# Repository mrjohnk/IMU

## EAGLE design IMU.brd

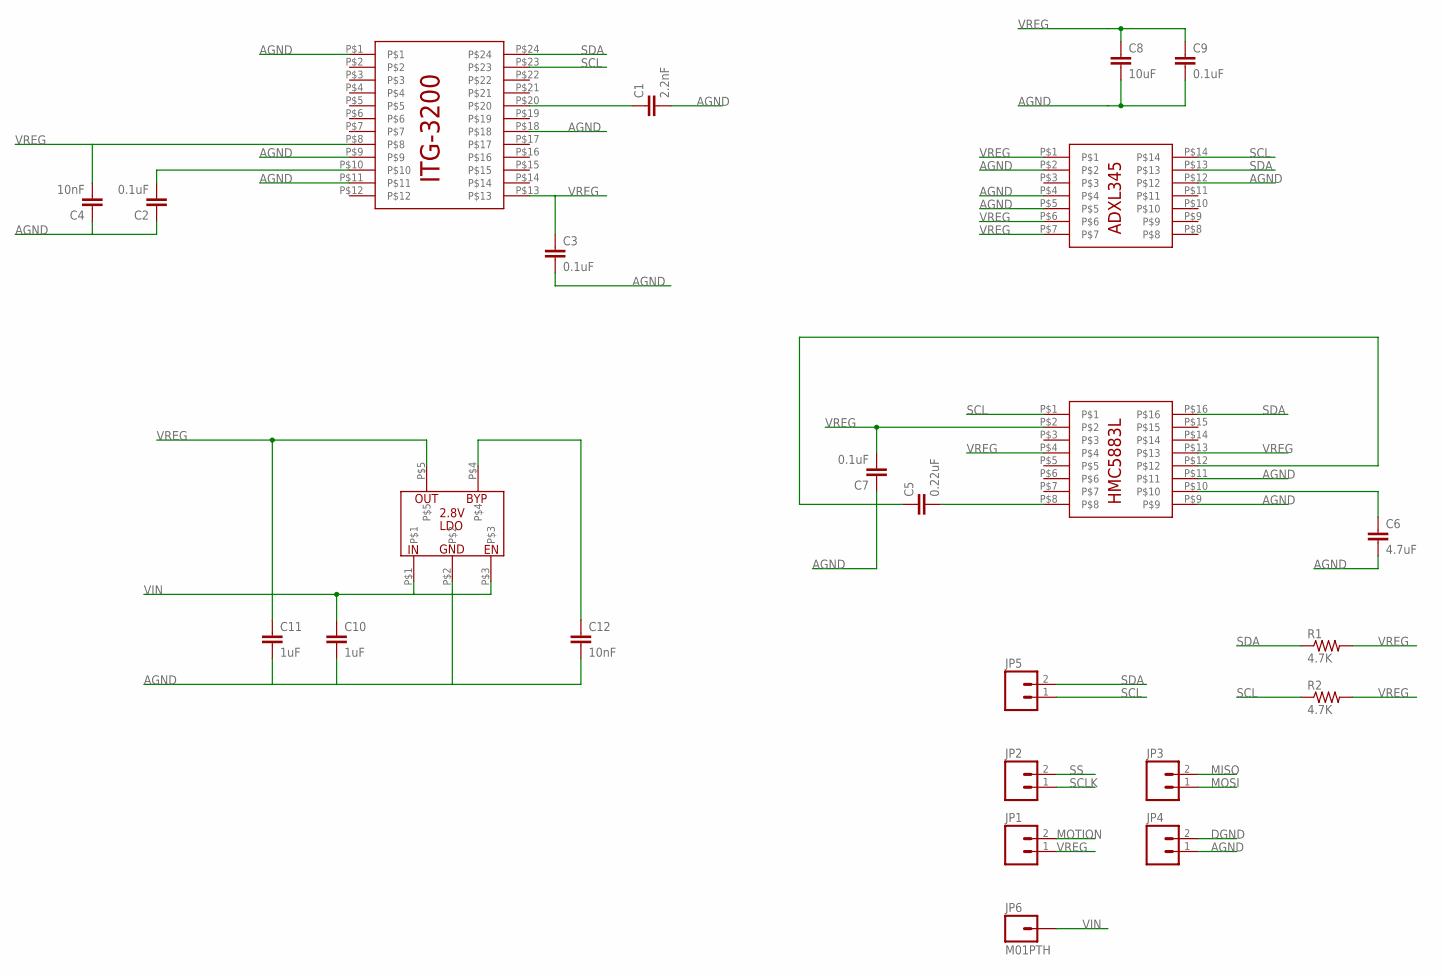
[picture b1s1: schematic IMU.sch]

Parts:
C1: 2.2nF; 0603-CAP
C2, C3, C7, C9: 0.1uF; 0603-CAP
C4, C12: 10nF; 0603-CAP
C5: 0.22uF; 0603-CAP
C6: 4.7uF; 0603-CAP
C8: 10uF; 0603-CAP
C10, C11: 1uF; 0603-CAP
JP1, JP2, JP3, JP4, JP5: M02PTH; 1X02
JP6: M01PTH; 1X01
R1, R2: 4.7K; 0603-RES
U$2: ADXL345
U$3: HMC5883L
U$4: ITG-3200
U$5: NCP700BMT28TBG__2.8V_LDO

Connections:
AGND: C1.2, C2.1, C3.2, C4.1, C6.2, C7.1, C8.2, C9.2, C10.2, C11.2, C12.2, JP4.1, U$2.P$2, U$2.P$4, U$2.P$5, U$2.P$12, U$3.P$9, U$3.P$11, U$4.P$1, U$4.P$9, U$4.P$11, U$4.P$18, U$5.P$2
DGND: JP4.2
MISO: JP3.2
MOSI: JP3.1
MOTION: JP1.2
unnamed: C1.1, U$4.P$20
unnamed: C2.2, U$4.P$10
unnamed: C5.2, U$3.P$8
unnamed: C5.1, U$3.P$12
unnamed: C6.1, U$3.P$10
unnamed: C12.1, U$5.P$4
SCL: JP5.1, R2.1, U$2.P$14, U$3.P$1, U$4.P$23
SCLK: JP2.1
SDA: JP5.2, R1.1, U$2.P$13, U$3.P$16, U$4.P$24
SS: JP2.2
VIN: C10.1, JP6.1, U$5.P$1, U$5.P$3
VREG: C3.1, C4.2, C7.2, C8.1, C9.1, C11.1, JP1.1, R1.2, R2.2, U$2.P$1, U$2.P$6, U$2.P$7, U$3.P$2, U$3.P$4, U$3.P$13, U$4.P$8, U$4.P$13, U$5.P$5

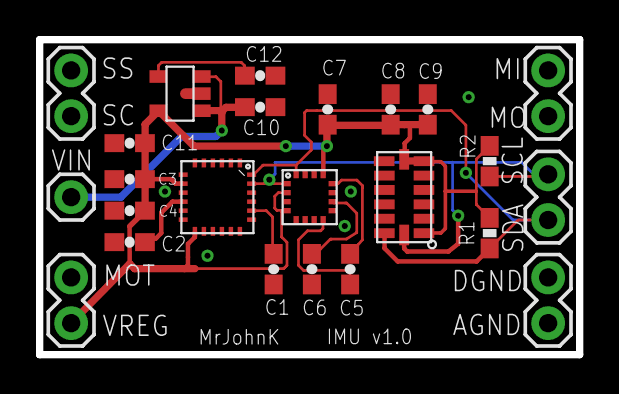
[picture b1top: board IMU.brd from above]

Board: 2 copper layers, 30.0 x 17.5 mm, 24 parts (0 on the bottom side), 11 nets.

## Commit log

2014-07-27 IMU based upon Razor IMU sensor stick

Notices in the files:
parts and their libraries:
SparkFun-Connectors: Licensing: CC v3.0 Share-Alike You are welcome to use this library for commercial purposes.
